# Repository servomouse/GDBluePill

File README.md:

# GDBluePill
This is a Blue Pill compatible board with GD32F103C8T6

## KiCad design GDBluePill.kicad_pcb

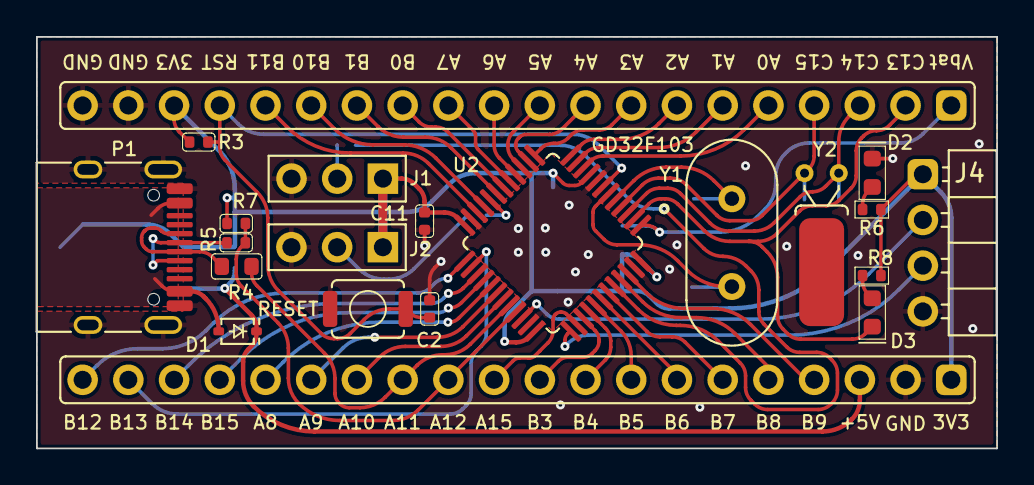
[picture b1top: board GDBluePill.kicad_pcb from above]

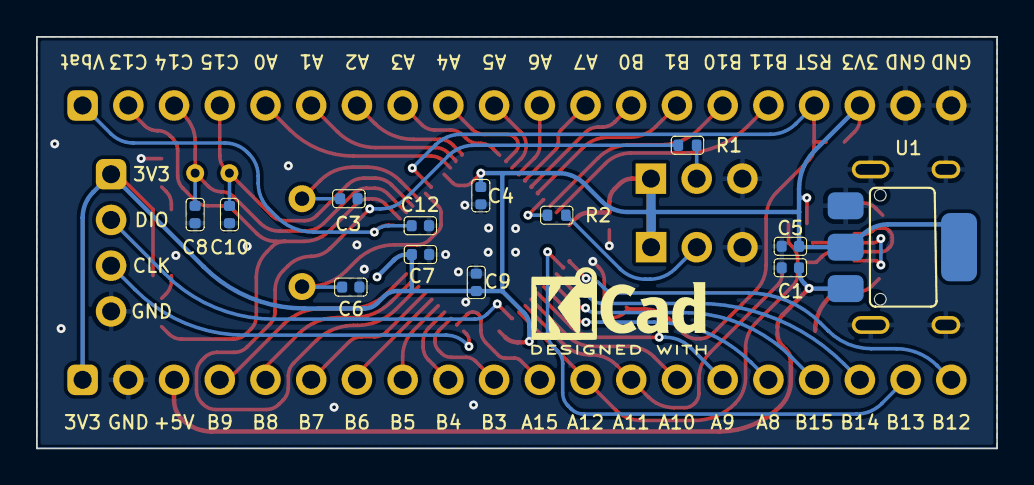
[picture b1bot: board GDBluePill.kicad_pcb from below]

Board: 2 copper layers, 53.3 x 22.9 mm, 34 parts (13 on the bottom side), 50 nets.

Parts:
C1, C2, C3, C4, C5, C6, C7, C8, C9, C10, C11, C12: C; C_0402
D1: D; D_SOD-323
D2, D3: LED; LED_0603
J1, J2: Conn_01x03; PinHeader_1x03_P2.54mm
J3, J5: Conn_01x20; PinHeader_1x20_P2.54mm
J4: SWD; PinHeader_1x04_P2.54mm_Horizontal
P1: USB_C_Plug_USB2.0; USB_C
R1, R2, R5, R7: 10k; R_0402
R3, R6, R8: 47k; R_0402
R4: 10k; R_0603
SW1: RESET; SW_Push_Alps_SKRK
U1: AP1117-33; SOT-223-3_TabPin2
U2: STM32F103C8Tx; LQFP-48_7x7mm_P0.5mm
Y1: 8MHz; Crystal_HC49-4H
Y2: 32.768; Crystal_DS26_D2.0mm_L6.0mm

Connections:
+3V3: C4.1, C5.1, C7.1, C9.1, C11.1, J1.1, J2.1, J3.18, J4.1, J5.1, R3.1, R6.1, R7.2, R8.1, U1.2 (VO), U2.9 (VDDA), U2.24 (VDD), U2.36 (VDD), U2.48 (VDD)
+5V: C1.1, D1.1 (K), J5.3, U1.3 (VI)
BOOT0: R1.1, U2.44 (BOOT0)
BOOT1: R2.1, U2.20 (PB2)
GND: C1.2, C2.2, C3.2, C4.2, C5.2, C6.2, C7.2, C8.2, C9.2, C10.2, C11.2, C12.2, D2.1 (K), J1.3, J2.3, J3.19, J3.20, J4.4, J5.2, P1.A1 (GND), P1.A12 (GND), P1.S1 (SHIELD), SW1.1 (A), U1.1 (GND), U2.8 (VSSA), U2.23 (VSS), U2.35 (VSS), U2.47 (VSS)
unnamed: D1.2 (A), P1.A4 (VBUS), P1.A9 (VBUS)
unnamed: D2.2 (A), R6.2
unnamed: D3.2 (A), R8.2
unnamed: J1.2, R1.2
unnamed: J2.2, R2.2
unnamed: P1.A6 (D+), R5.1
unnamed: P1.A7 (D-), R4.1
OSC_IN: C3.1, U2.5 (PD0), Y1.1
OSC_OUT: C6.1, U2.6 (PD1), Y1.2
PA0: J3.5, U2.10 (PA0)
PA1: J3.6, U2.11 (PA1)
PA2: J3.7, U2.12 (PA2)
PA3: J3.8, U2.13 (PA3)
PA4: J3.9, U2.14 (PA4)
PA5: J3.10, U2.15 (PA5)
PA6: J3.11, U2.16 (PA6)
PA7: J3.12, U2.17 (PA7)
PA8: J5.16, U2.29 (PA8)
PA9: J5.15, U2.30 (PA9)
PA10: J5.14, U2.31 (PA10)
PA11: J5.13, R4.2, U2.32 (PA11)
PA12: J5.12, R5.2, R7.1, U2.33 (PA12)
PA15: J5.11, U2.38 (PA15)
PB0: J3.13, U2.18 (PB0)
PB1: J3.14, U2.19 (PB1)
PB3: J5.10, U2.39 (PB3)
PB4: J5.9, U2.40 (PB4)
PB5: J5.8, U2.41 (PB5)
PB6: J5.7, U2.42 (PB6)
PB7: J5.6, U2.43 (PB7)
PB8: J5.5, U2.45 (PB8)
PB9: J5.4, U2.46 (PB9)
PB10: J3.15, U2.21 (PB10)
PB11: J3.16, U2.22 (PB11)
PB12: J5.20, U2.25 (PB12)
PB13: J5.19, U2.26 (PB13)
PB14: J5.18, U2.27 (PB14)
PB15: J5.17, U2.28 (PB15)
PC13: D3.1 (K), J3.2, U2.2 (PC13)
PC14: C8.1, J3.3, U2.3 (PC14), Y2.2
PC15: C10.1, J3.4, U2.4 (PC15), Y2.1
RESET: C2.1, J3.17, R3.2, SW1.2 (B), U2.7 (NRST)
SWCLK: J4.3, U2.37 (PA14)
SWDIO: J4.2, U2.34 (PA13)
VBAT: C12.1, J3.1, U2.1 (VBAT)

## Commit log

2022-07-02 Init
2022-07-02 Components values updated
2022-09-07 USB connector and pull-up resistor value fixed
